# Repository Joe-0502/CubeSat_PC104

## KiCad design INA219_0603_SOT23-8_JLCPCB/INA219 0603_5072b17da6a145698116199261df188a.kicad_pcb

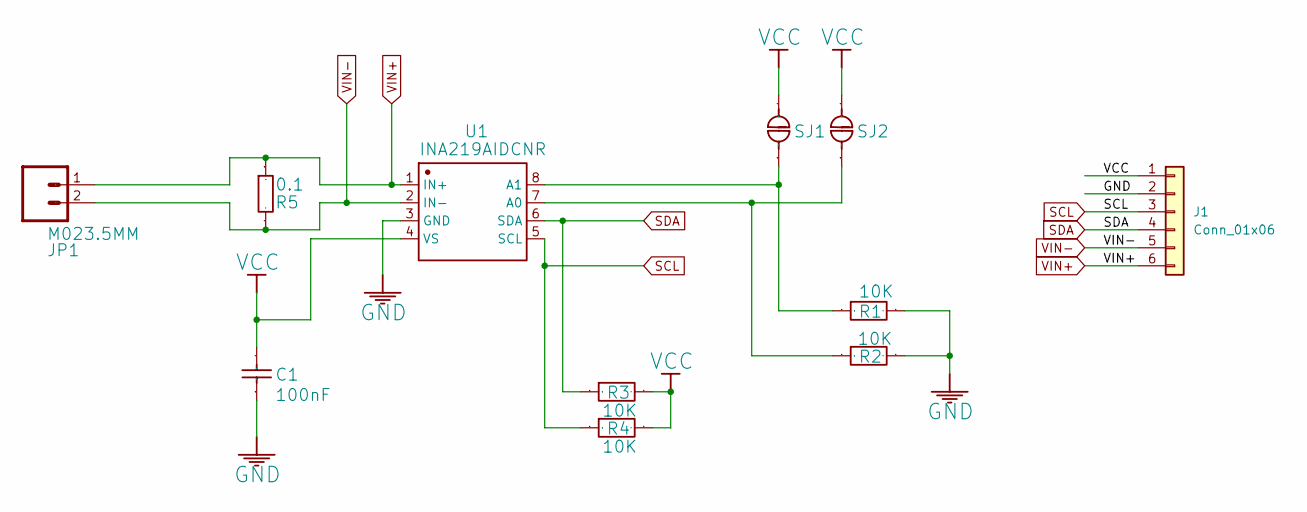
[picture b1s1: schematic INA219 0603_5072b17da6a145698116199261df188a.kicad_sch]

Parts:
C1: 100nF; C_0603_1608Metric
J1: Conn_01x06; PinHeader_1x06_P2.54mm_Vertical
JP1: M023.5MM; TerminalBlock_4Ucon_1x02_P3.50mm_Horizontal_small
R1, R2, R3, R4: 10K; R_0603_1608Metric
R5: 0.1; R_2512
SJ1, SJ2: SOLDERJUMPERNC_TR; SolderJumper_2
U1: INA219AIDCNR; SOT-23-8

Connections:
GND: C1.1, J1.2, R1.2, R2.2, U1.3 (GND)
unnamed: R2.1, SJ2.1, U1.7 (A0)
unnamed: R1.1, SJ1.1, U1.8 (A1)
SCL: J1.3, R4.1, U1.5 (SCL)
SDA: J1.4, R3.1, U1.6 (SDA)
VCC: C1.2, J1.1, R3.2, R4.2, SJ1.2, SJ2.2, U1.4 (VS)
VIN+: J1.6, JP1.1, R5.1, U1.1 (IN+)
VIN-: J1.5, JP1.2, R5.2, U1.2 (IN-)

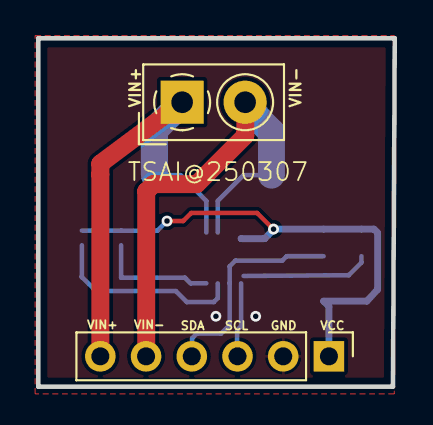
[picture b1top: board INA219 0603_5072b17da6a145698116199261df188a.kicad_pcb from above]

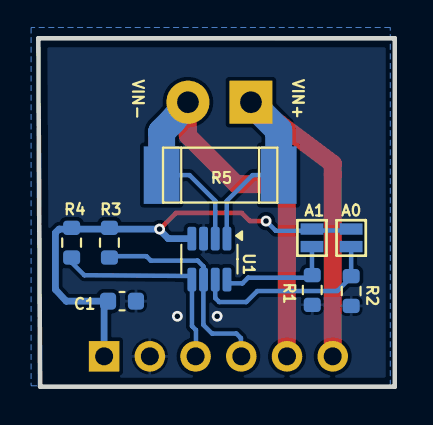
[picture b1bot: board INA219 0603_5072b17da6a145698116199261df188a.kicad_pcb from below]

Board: 2 copper layers, 19.8 x 19.4 mm, 11 parts (9 on the bottom side), 8 nets.

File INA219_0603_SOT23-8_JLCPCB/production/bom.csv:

Designator,Footprint,Quantity,Value,LCSC Part #
C1,0603,1,100nF,
J1,PinHeader_1x06_P2.54mm_Vertical,1,Conn_01x06,
JP1,TerminalBlock_4Ucon_1x02_P3.50mm_Horizontal_small,1,M023.5MM,
"R1, R2, R3, R4",0603,4,10K,
R5,R_2512,1,0.1,
"SJ1, SJ2",SolderJumper_2,2,SOLDERJUMPERNC_TR,
U1,SOT-23-8,1,INA219AIDCNR,

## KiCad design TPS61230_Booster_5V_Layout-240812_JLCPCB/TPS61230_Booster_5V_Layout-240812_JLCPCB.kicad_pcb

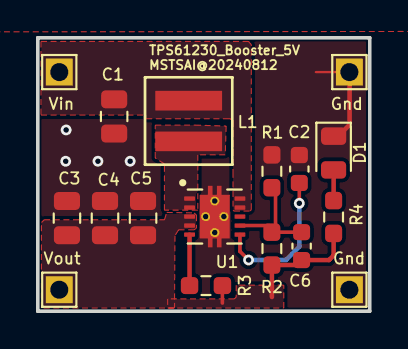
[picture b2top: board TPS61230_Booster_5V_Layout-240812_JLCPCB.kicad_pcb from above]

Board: 2 copper layers, 18.4 x 15.2 mm, 17 parts (0 on the bottom side), 8 nets.

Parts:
C1, C3, C4, C5: 22uF; C_0805_2012Metric
C2: 10nF; C_0603_1608Metric
C6: DNI/18pF; C_0603_1608Metric
D1: LED; LED_0805_2012Metric
L1: 1uH; IND_EXLA-0402_EAT
R1: 100K; R_0603_1608Metric_Pad0.98x0.95mm_HandSolder
R2: 402K; R_0603_1608Metric_Pad0.98x0.95mm_HandSolder
R3: 1M0; R_0603_1608Metric_Pad0.98x0.95mm_HandSolder
R4: 1K; R_0603_1608Metric_Pad0.98x0.95mm_HandSolder
TP5: VIN; TestPoint_THTPad_1.5x1.5mm_Drill0.7mm
TP6, TP8: GND; TestPoint_THTPad_1.5x1.5mm_Drill0.7mm
TP7: VOUT; TestPoint_THTPad_1.5x1.5mm_Drill0.7mm
U1: VREG_V62_16624-01YE_TPS61230DRCR; TPS61230DRCR

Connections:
/FB: C6.2, R1.1, R2.2, U1.7 (FB)
/VIN: C1.1, L1.1, TP5.1, U1.9 (EN), U1.10 (VIN)
GND: C1.2, C2.2, C3.2, C4.2, C5.2, D1.1 (K), R1.2, TP6.1, TP8.1, U1.11 (GND), U1.12 (GND), U1.13 (GND), U1.14 (GND), U1.15
unnamed: D1.2 (A), R4.2
unnamed: R3.2, U1.5 (PG)
unnamed: C2.1, U1.6 (SS)
unnamed: L1.2, U1.1 (SW), U1.2 (SW__1)
unnamed: C3.1, C4.1, C5.1, C6.1, R2.1, R3.1, R4.1, TP7.1, U1.3 (VOUT), U1.4 (VOUT__1)

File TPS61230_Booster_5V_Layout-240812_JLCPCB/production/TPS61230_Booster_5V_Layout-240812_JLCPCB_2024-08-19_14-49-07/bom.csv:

Designator,Footprint,Quantity,Value,LCSC Part #
"C1, C3, C4, C5",0805,4,22uF,
C2,0603,1,10nF,
C6,0603,1,DNI/18pF,
D1,0805,1,LED,
L1,IND_EXLA-0402_EAT,1,1uH,
R1,0603,1,100K,
R2,0603,1,402K,
R3,0603,1,1M0,
R4,0603,1,1K,
TP5,TestPoint_THTPad_1.5x1.5mm_Drill0.7mm,1,VIN,
"TP6, TP8",TestPoint_THTPad_1.5x1.5mm_Drill0.7mm,2,GND,
TP7,TestPoint_THTPad_1.5x1.5mm_Drill0.7mm,1,VOUT,
U1,TPS61230DRCR,1,TPS61230DRCR,
